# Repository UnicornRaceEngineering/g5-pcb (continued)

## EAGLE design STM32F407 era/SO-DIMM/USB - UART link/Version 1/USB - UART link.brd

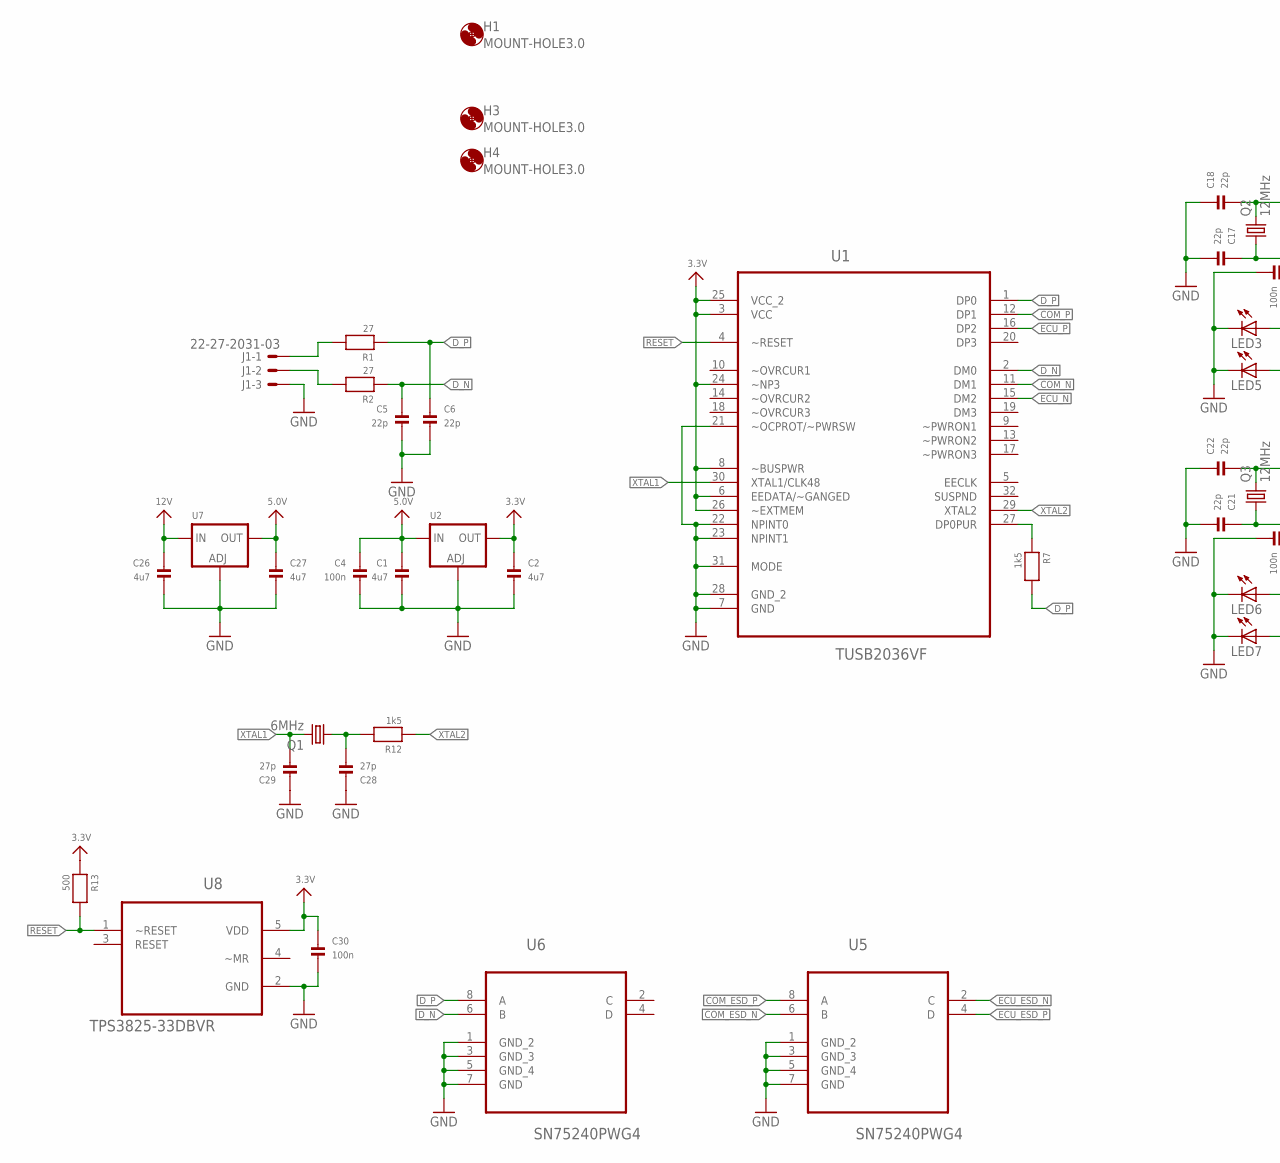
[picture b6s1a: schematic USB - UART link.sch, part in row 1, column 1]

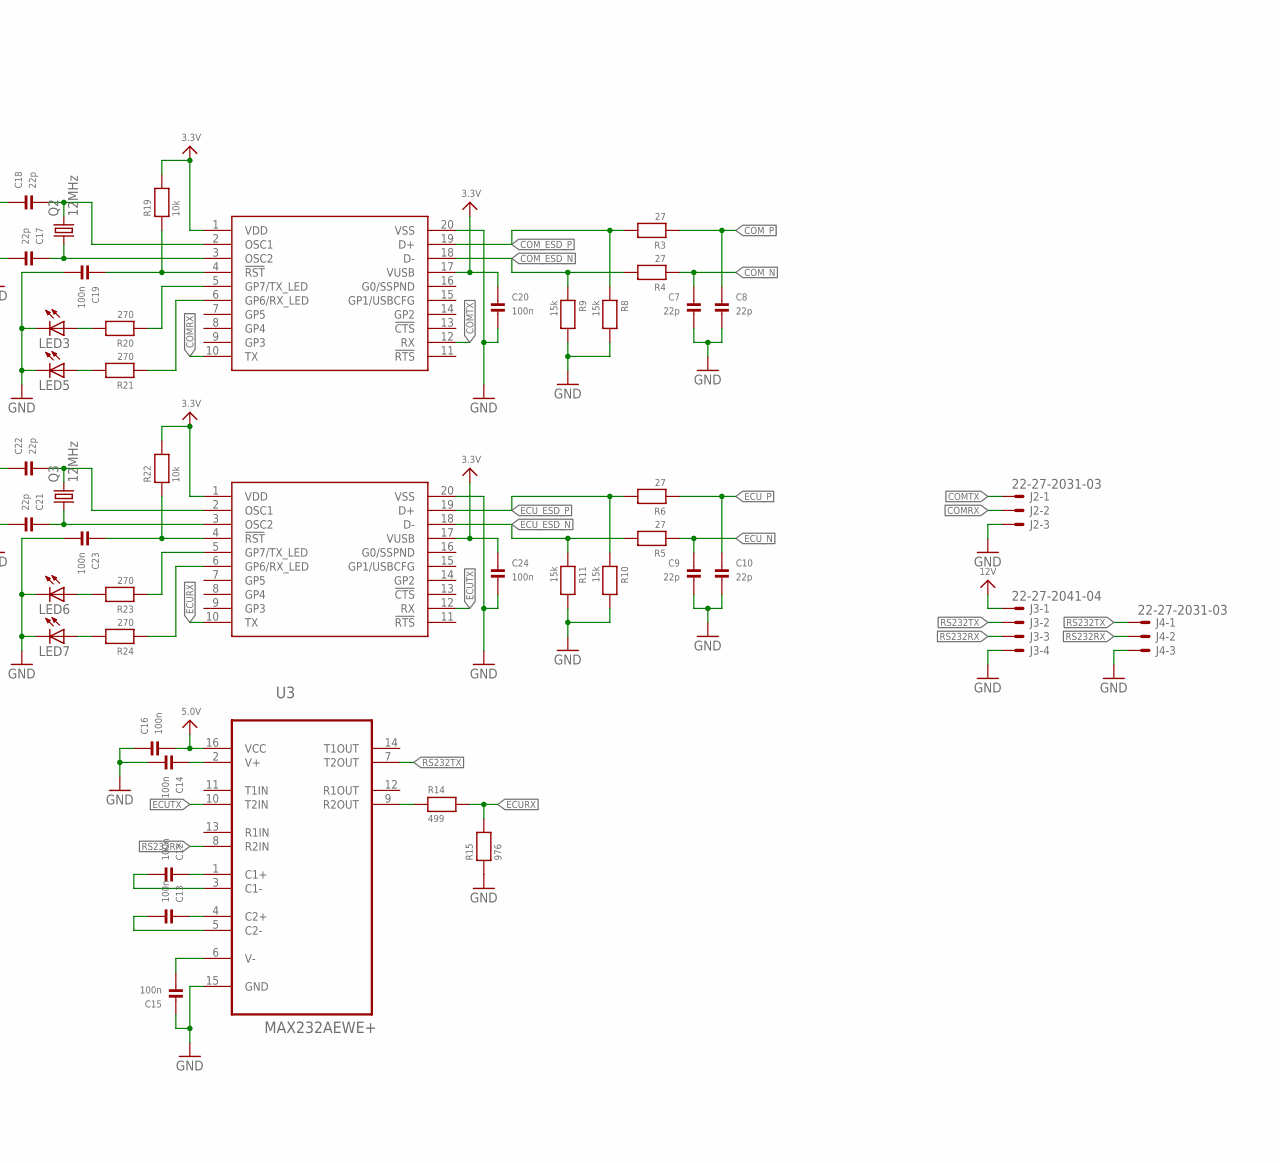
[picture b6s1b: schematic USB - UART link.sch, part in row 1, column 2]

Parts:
C1, C2, C26, C27: 4u7; _0805
C4, C12, C13, C14, C15, C16, C19, C20, C23, C24, C30: 100n; _0603
C5, C6, C7, C8, C9, C10, C17, C18, C21, C22: 22p; _0603
C28, C29: 27p; _0603
H1, H3, H4: MOUNT-HOLE3.0; 3,0
J1, J2, J4: 22-27-2031-03; 6410-03
J3: 22-27-2041-04; 6410-04
LED3, LED5, LED6, LED7: LEDCHIPLED_0805; CHIPLED_0805
Q1: 6MHz; HC49/S
Q2, Q3: 12MHz; HC49/S
R1, R2, R3, R4, R5, R6: 27; _0603
R7, R12: 1k5; _0603
R8, R9, R10, R11: 15k; _0603
R13: 500; _0603
R14: 499; _0603
R15: 976; _0603
R19, R22: 10k; _0603
R20, R21, R23, R24: 270; _0603
U1: TUSB2036VF; QFP80P900X900X145-32N
U2, U7: LM1117SOT223-REFLOW; SOT223-R
U3: MAX232AEWE+; SOIC127P1032X265-16N
U5, U6: SN75240PWG4; SOP65P640X120-8N
U8: TPS3825-33DBVR; SOT95P280X145-5N
U$24, U$29: MCP2200; SO20L

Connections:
3.3V: C2.1, C20.1, C24.1, C30.1, R13.1, R19.2, R22.2, U1.3 (VCC), U1.6 (EEDATA/~GANGED), U1.8 (~BUSPWR), U1.24 (~NP3), U1.25 (VCC_2), U1.26 (~EXTMEM), U2.2 (OUT), U8.5 (VDD), U$24.1 (VDD), U$24.17 (VUSB), U$29.1 (VDD), U$29.17 (VUSB)
5.0V: C1.1, C4.1, C16.2, C27.1, U2.3 (IN), U3.16 (VCC), U7.2 (OUT)
12V: C26.1, J3.1, U7.3 (IN)
COMRX: J2.2, U$24.10 (TX)
COMTX: J2.1, U$24.12 (RX)
COM_ESD_N: R4.2, R9.1, U5.6 (B), U$24.18 (D-)
COM_ESD_P: R3.2, R8.1, U5.8 (A), U$24.19 (D+)
COM_N: C7.1, R4.1, U1.11 (DM1)
COM_P: C8.1, R3.1, U1.12 (DP1)
DO_N: J1.2, R2.2
DO_P: J1.1, R1.2
D_N: C5.1, R2.1, U1.2 (DM0), U6.6 (B)
D_P: C6.1, R1.1, R7.2, U1.1 (DP0), U6.8 (A)
ECURX: R14.2, R15.2, U$29.10 (TX)
ECUTX: U3.10 (T2IN), U$29.12 (RX)
ECU_ESD_N: R5.2, R11.1, U5.2 (C), U$29.18 (D-)
ECU_ESD_P: R6.2, R10.1, U5.4 (D), U$29.19 (D+)
ECU_N: C9.1, R5.1, U1.15 (DM2)
ECU_P: C10.1, R6.1, U1.16 (DP2)
GND: C1.2, C2.2, C4.2, C5.2, C6.2, C7.2, C8.2, C9.2, C10.2, C14.2, C15.1, C16.1, C17.2, C18.1, C19.2, C20.2, C21.2, C22.1, C23.2, C24.2, C26.2, C27.2, C28.1, C29.1, C30.2, J1.3, J2.3, J3.4, J4.3, LED3.C, LED5.C, LED6.C, LED7.C, R8.2, R9.2, R10.2, R11.2, R15.1, U1.7 (GND), U1.21 (~OCPROT/~PWRSW), U1.22 (NPINT0), U1.23 (NPINT1), U1.28 (GND_2), U1.31 (MODE), U2.1 (ADJ), U3.15 (GND), U5.1 (GND_2), U5.3 (GND_3), U5.5 (GND_4), U5.7 (GND), U6.1 (GND_2), U6.3 (GND_3), U6.5 (GND_4), U6.7 (GND), U7.1 (ADJ), U8.2 (GND), U$24.20 (VSS), U$29.20 (VSS)
unnamed: R14.1, U3.9 (R2OUT)
unnamed: R7.1, U1.27 (DP0PUR)
unnamed: C13.1, U3.4 (C2+)
unnamed: C12.2, U3.3 (C1-)
unnamed: C12.1, U3.1 (C1+)
unnamed: C28.2, Q1.1, R12.2
unnamed: C15.2, U3.6 (V-)
unnamed: C14.1, U3.2 (V+)
unnamed: C13.2, U3.5 (C2-)
unnamed: C22.2, Q3.2, U$29.2 (OSC1)
unnamed: C18.2, Q2.2, U$24.2 (OSC1)
unnamed: C17.1, Q2.1, U$24.3 (OSC2)
unnamed: C21.1, Q3.1, U$29.3 (OSC2)
unnamed: R21.1, U$24.6 (GP6/RX_LED)
unnamed: R20.1, U$24.5 (GP7/TX_LED)
unnamed: C19.1, R19.1, U$24.4 (!RST)
unnamed: R24.1, U$29.6 (GP6/RX_LED)
unnamed: R23.1, U$29.5 (GP7/TX_LED)
unnamed: LED3.A, R20.2
unnamed: LED5.A, R21.2
unnamed: C23.1, R22.1, U$29.4 (!RST)
unnamed: LED6.A, R23.2
unnamed: LED7.A, R24.2
RESET: R13.2, U1.4 (~RESET), U8.1 (~RESET)
RS232RX: J3.3, J4.2, U3.8 (R2IN)
RS232TX: J3.2, J4.1, U3.7 (T2OUT)
XTAL1: C29.2, Q1.2, U1.30 (XTAL1/CLK48)
XTAL2: R12.1, U1.29 (XTAL2)

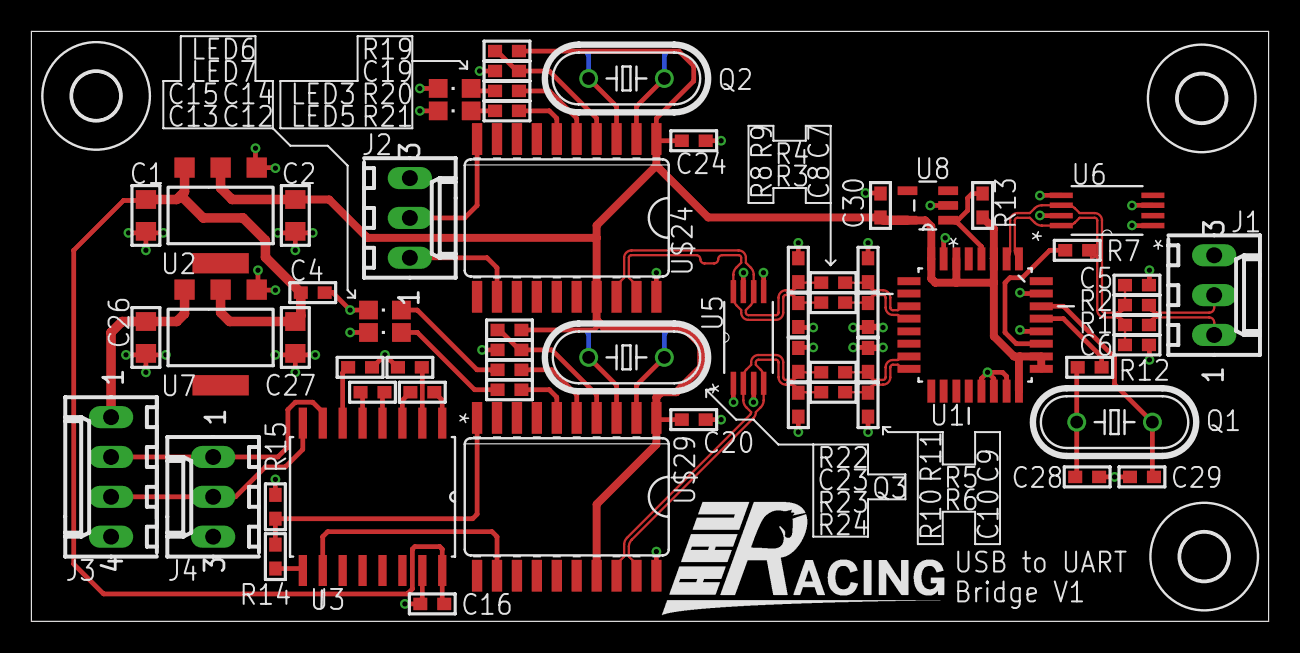
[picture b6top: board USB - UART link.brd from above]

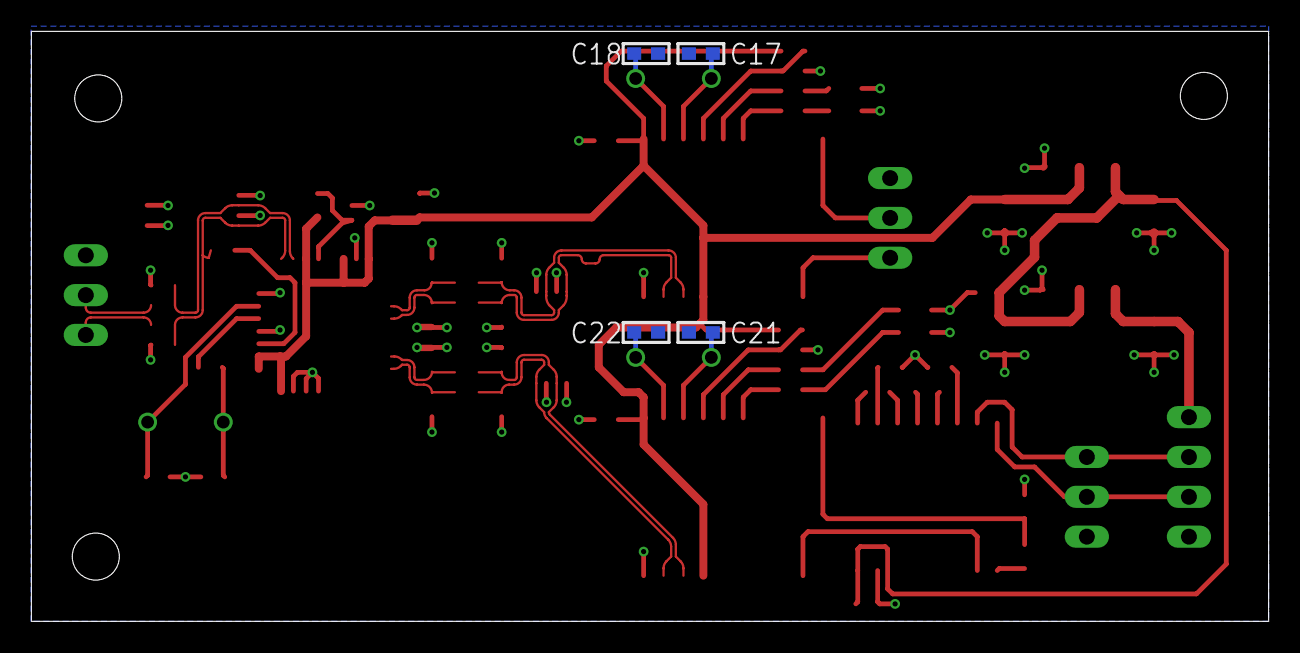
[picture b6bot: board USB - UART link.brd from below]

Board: 2 copper layers, 78.9 x 37.6 mm, 71 parts (4 on the bottom side), 48 nets.

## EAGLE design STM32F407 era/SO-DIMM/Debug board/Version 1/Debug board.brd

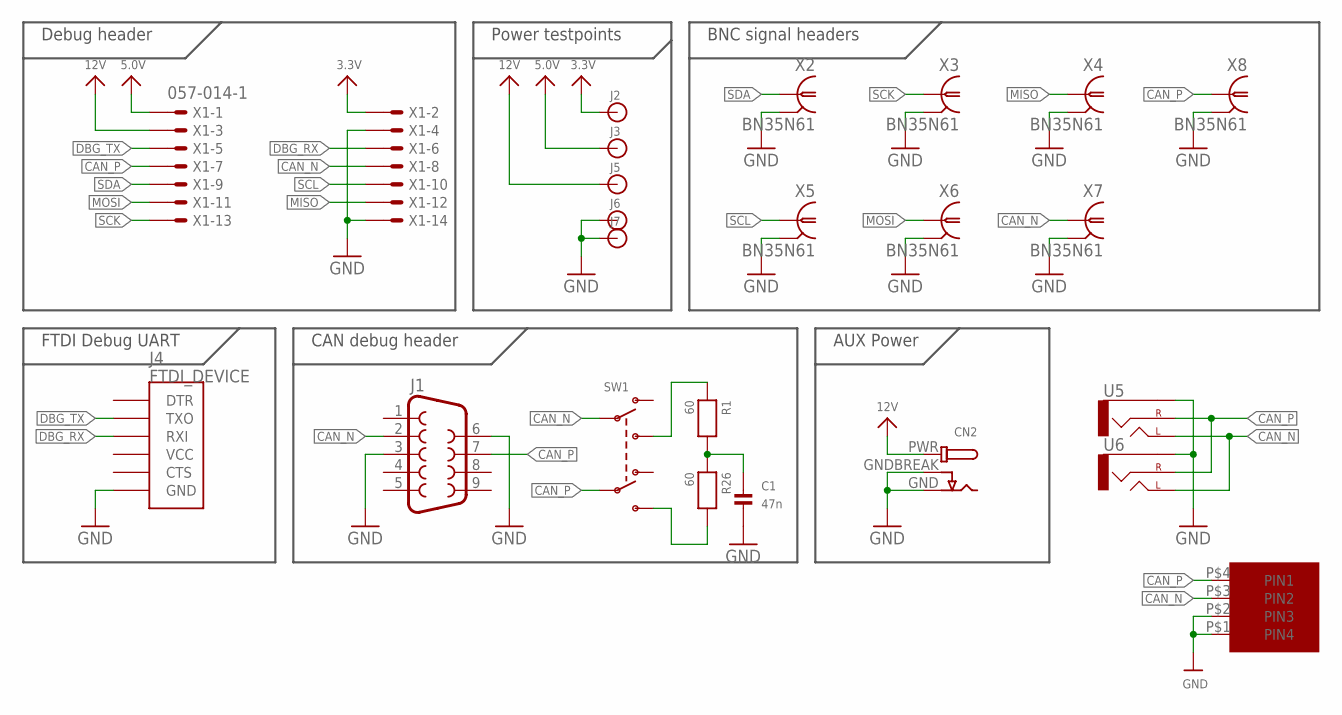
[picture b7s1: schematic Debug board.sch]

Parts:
C1: 47n; _0603
CN2: DCBARRELPTH; DCJACK_2MM_PTH
J1: DB9FEMALE; DB9
J2, J3, J5, J6, J7: BANANA_CONN
J4: FTDI_DEVICE; FTDI_DEVICE_SIDE
R1, R26: 60; _0603
SW1: SWITCH_DPDT; DPDT_SMT_JS202011SCQN
U5, U6: AUDIO-JACKPTH; AUDIO-JACK
U$21: MICROFIT4; 43045-0400
X1: 057-014-1
X2, X3, X4, X5, X6, X7, X8: BN35N61; B35N61

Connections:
3.3V: J2.P$1, X1.2
5.0V: J3.P$1, X1.1
12V: CN2.PWR, J5.P$1, X1.3
CAN_N: J1.2, SW1.P$2 (P1), U5.TIP (LEFT), U6.TIP (LEFT), U$21.P$3 (PIN2), X1.8, X7.1
CAN_P: J1.7, SW1.P$5 (P2), U5.RING (RIGHT), U6.RING (RIGHT), U$21.P$4 (PIN1), X1.7, X8.1
DBG_RX: J4.P$3 (RXI), X1.6
DBG_TX: J4.P$2 (TXO), X1.5
GND: C1.2, CN2.GND, CN2.GNDBREAK, J1.3, J1.6, J4.P$6 (GND), J6.P$1, J7.P$1, U5.SLEEVE, U6.SLEEVE, U$21.P$1 (PIN4), U$21.P$2 (PIN3), X1.4, X1.14, X2.2 (GND), X2.3 (GND), X2.4 (GND), X2.5 (GND), X3.2 (GND), X3.3 (GND), X3.4 (GND), X3.5 (GND), X4.2 (GND), X4.3 (GND), X4.4 (GND), X4.5 (GND), X5.2 (GND), X5.3 (GND), X5.4 (GND), X5.5 (GND), X6.2 (GND), X6.3 (GND), X6.4 (GND), X6.5 (GND), X7.2 (GND), X7.3 (GND), X7.4 (GND), X7.5 (GND), X8.2 (GND), X8.3 (GND), X8.4 (GND), X8.5 (GND)
MISO: X1.12, X4.1
MOSI: X1.11, X6.1
unnamed: C1.1, R1.2, R26.1
unnamed: R1.1, SW1.P$3 (S1)
unnamed: R26.2, SW1.P$4 (S2)
SCK: X1.13, X3.1
SCL: X1.10, X5.1
SDA: X1.9, X2.1

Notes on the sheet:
FTDI Debug UART
Debug header
Power testpoints
CAN debug header
BNC signal headers
AUX Power

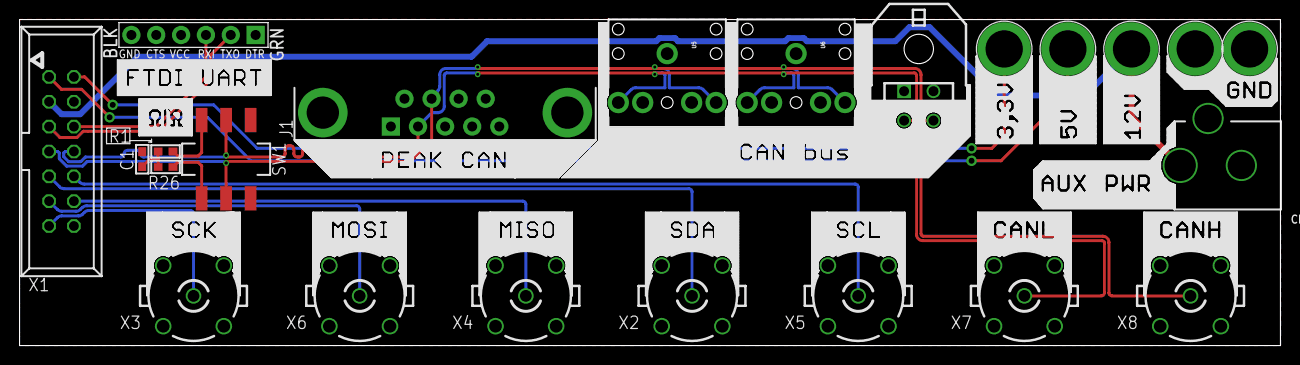
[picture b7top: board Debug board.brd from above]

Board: 2 copper layers, 128.9 x 33.3 mm, 23 parts (0 on the bottom side), 16 nets.

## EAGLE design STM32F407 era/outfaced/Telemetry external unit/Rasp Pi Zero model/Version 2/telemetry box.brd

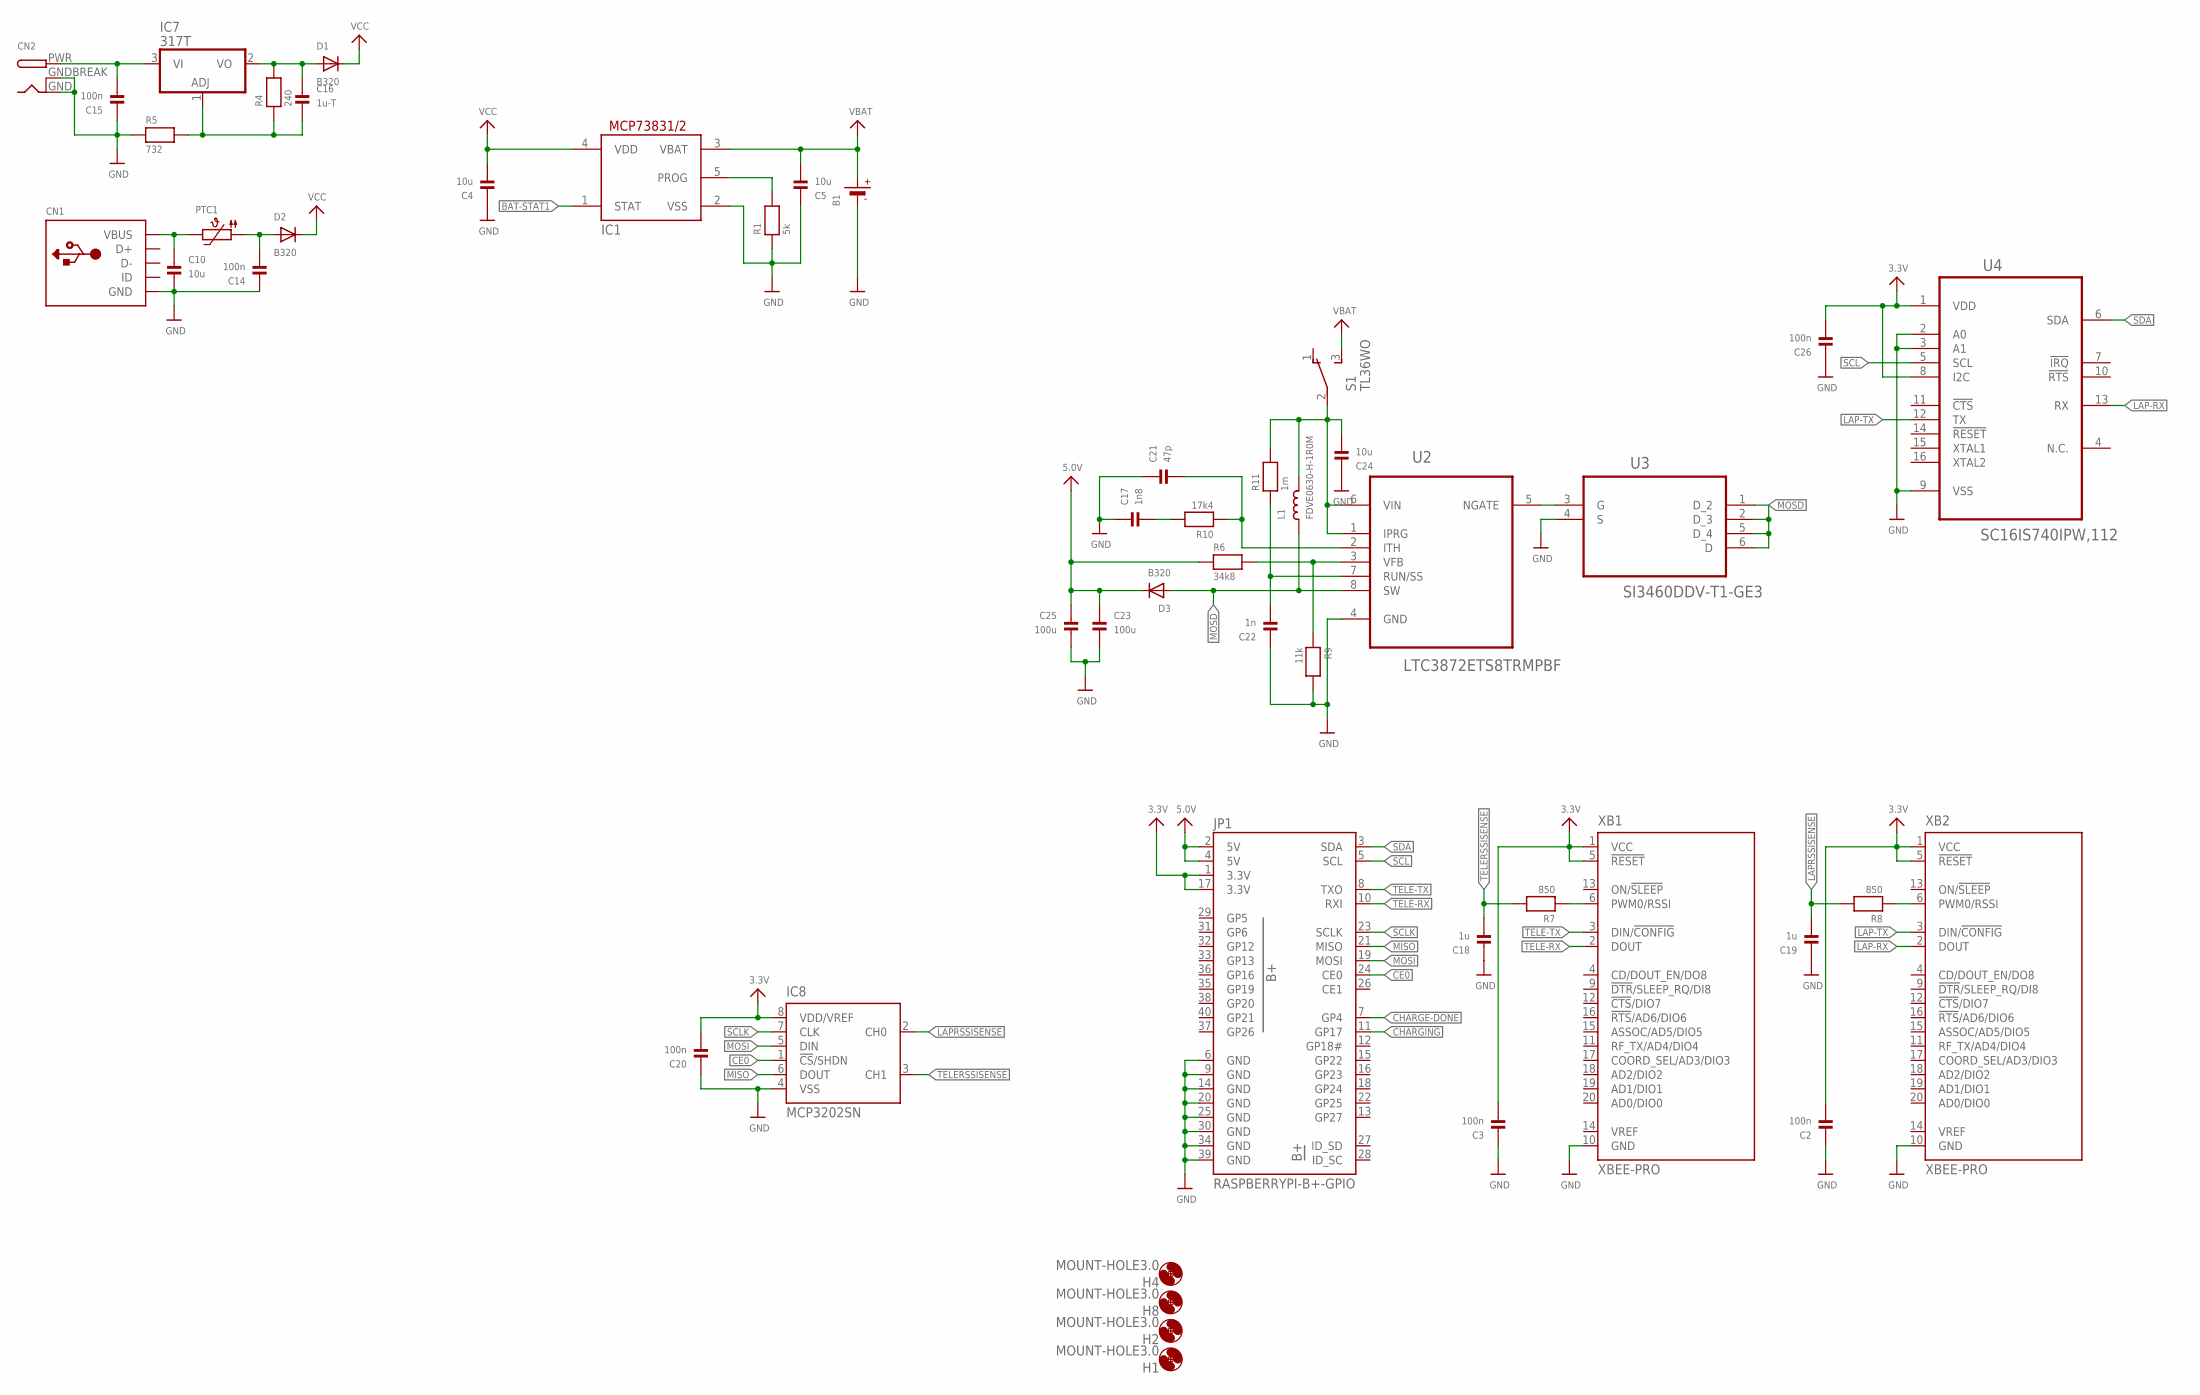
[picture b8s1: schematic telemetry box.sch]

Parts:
B1: BATTERY; JSTPH2
C2, C3, C14, C15, C20, C26: 100n; _0603
C4, C5, C10, C24: 10u; _0805
C16: 1u-T; _0603
C17: 1n8; _0603
C18, C19: 1u; _0603
C21: 47p; _0603
C22: 1n; _0603
C23, C25: 100u; 1206
CN1: USBMINIB; USB-MINIB
CN2: DCBARRELPTH; DCJACK_2MM_PTH
D1, D2, D3: B320; SMADIODE
H1, H2, H4, H8: MOUNT-HOLE3.0; 3,0
IC1: MCP73831/OT; SOT23-5L
IC7: 317T; TO220H
IC8: MCP3202SN; SO-08
JP1: RASPBERRYPI-B+-GPIO; 2X20-SHROUDED
L1: FDVE0630-H-1R0M; INDUCTOR_6X6MM_TDK_SLF6045
PTC1: PTC1206; 1206
R1: 5k; _0603
R4: 240; _0603
R5: 732; _0603
R6: 34k8; _0603
R7, R8: 850; _0603
R9: 11k; _0603
R10: 17k4; _0603
R11: 1m; _0603
S1: TL36WO; TL3XWO
U2: LTC3872ETS8TRMPBF; SOT65P280X100-8N
U3: SI3460DDV-T1-GE3; SOT95P285X110-6N
U4: SC16IS740IPW,112; SOP65P640X110-16N
XB1, XB2: XBEE-PRO

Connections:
3.3V: C2.2, C3.2, C20.2, C26.2, IC8.8 (VDD/VREF), JP1.1 (3.3V), JP1.17 (3.3V), U4.1 (VDD), U4.8 (I2C), XB1.1 (VCC), XB1.5 (!RESET), XB2.1 (VCC), XB2.5 (!RESET)
5.0V: C23.1, C25.1, D3.C, JP1.2 (5V), JP1.4 (5V), R6.1
BAT-STAT1: IC1.1 (STAT)
CE0: IC8.1 (!CS!/SHDN), JP1.24 (CE0)
CHARGE-DONE: JP1.7 (GP4)
CHARGING: JP1.11 (GP17)
GND: B1.1 (-), C2.1, C3.1, C4.1, C5.1, C10.2, C14.1, C15.1, C17.1, C18.1, C19.1, C20.1, C21.1, C22.1, C23.2, C24.1, C25.2, C26.1, CN1.GND, CN2.GND, CN2.GNDBREAK, IC1.2 (VSS), IC8.4 (VSS), JP1.6 (GND), JP1.9 (GND), JP1.14 (GND), JP1.20 (GND), JP1.25 (GND), JP1.30 (GND), JP1.34 (GND), JP1.39 (GND), R1.1, R5.1, R9.2, U2.4 (GND), U3.4 (S), U4.2 (A0), U4.3 (A1), U4.9 (VSS), XB1.10 (GND), XB2.10 (GND)
LAP-RX: U4.13 (RX), XB2.2 (DOUT)
LAP-TX: U4.12 (TX), XB2.3 (DIN/!CONFIG)
LAPRSSISENSE: C19.2, IC8.2 (CH0), R8.2
MISO: IC8.6 (DOUT), JP1.21 (MISO)
MOSD: D3.A, L1.P$1 (1), U2.8 (SW), U3.1 (D_2), U3.2 (D_3), U3.5 (D_4), U3.6 (D)
MOSI: IC8.5 (DIN), JP1.19 (MOSI)
unnamed: C24.2, L1.P$2 (2), R11.2, S1.2, U2.1 (IPRG), U2.6 (VIN)
unnamed: IC1.5 (PROG), R1.2
unnamed: C10.1, CN1.VBUS, PTC1.2
unnamed: C16.2, IC7.1 (ADJ), R4.1, R5.2
unnamed: R6.2, R9.1, U2.3 (VFB)
unnamed: C16.1, D1.A, IC7.2 (VO), R4.2
unnamed: C14.2, D2.A, PTC1.1
unnamed: C15.2, CN2.PWR, IC7.3 (VI)
unnamed: R7.1, XB1.6 (PWM0/RSSI)
unnamed: R8.1, XB2.6 (PWM0/RSSI)
unnamed: U2.5 (NGATE), U3.3 (G)
unnamed: C17.2, R10.2
unnamed: C21.2, R10.1, U2.2 (ITH)
unnamed: C22.2, R11.1, U2.7 (RUN/SS)
SCL: JP1.5 (SCL), U4.5 (SCL)
SCLK: IC8.7 (CLK), JP1.23 (SCLK)
SDA: JP1.3 (SDA), U4.6 (SDA)
TELE-RX: JP1.10 (RXI), XB1.2 (DOUT)
TELE-TX: JP1.8 (TXO), XB1.3 (DIN/!CONFIG)
TELERSSISENSE: C18.2, IC8.3 (CH1), R7.2
VBAT: B1.2 (+), C5.2, IC1.3 (VBAT), S1.3 (S)
VCC: C4.2, D1.C, D2.C, IC1.4 (VDD)

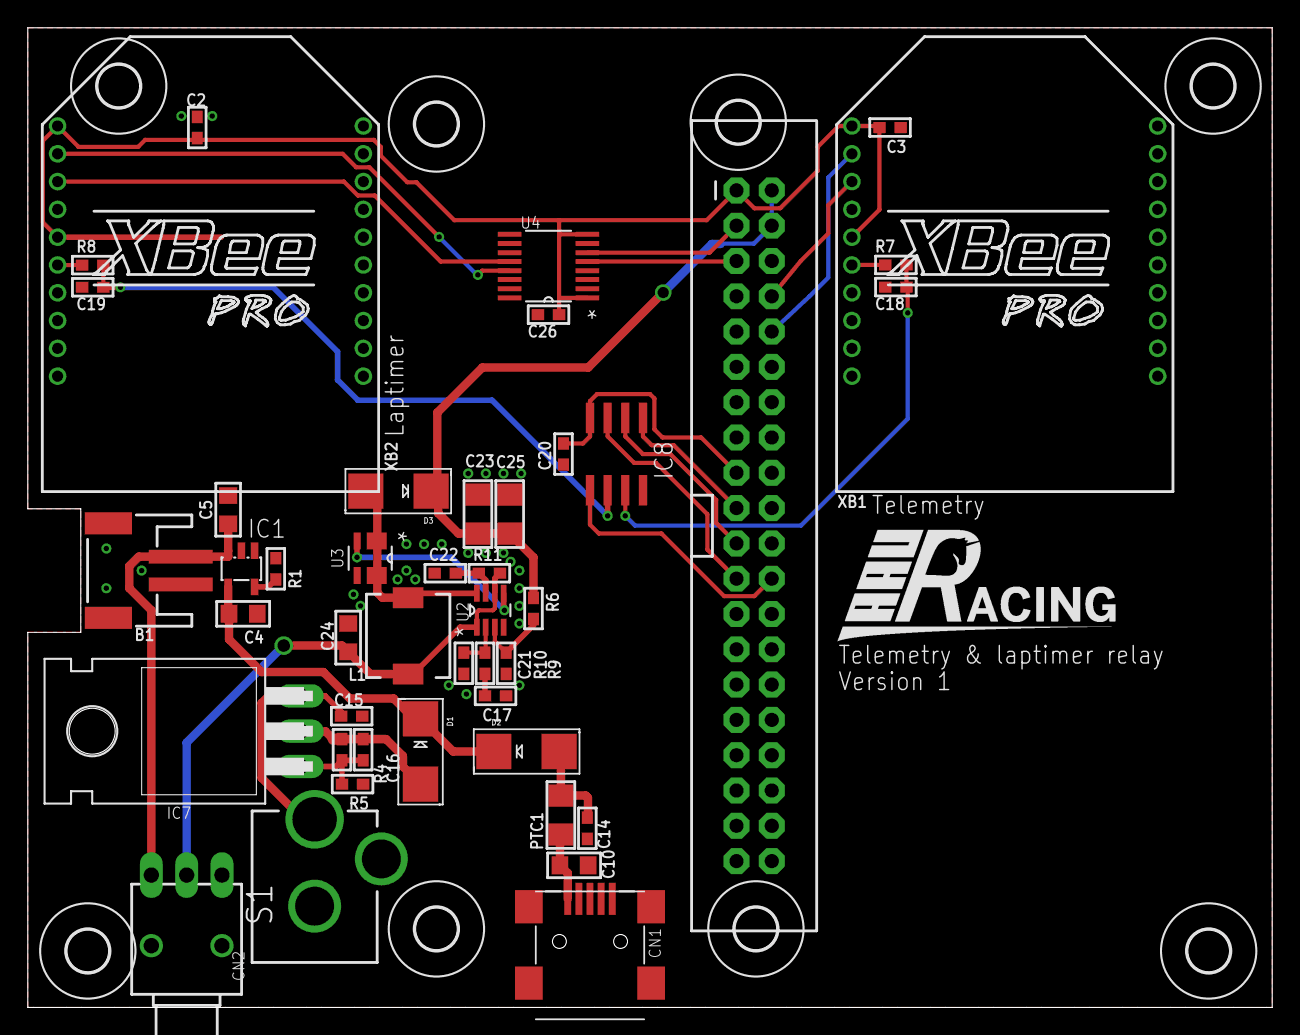
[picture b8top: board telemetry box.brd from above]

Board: 2 copper layers, 89.5 x 70.5 mm, 53 parts (0 on the bottom side), 32 nets.

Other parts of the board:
H3, H5, H6, H7: MOUNT-HOLE3.0; 3,0

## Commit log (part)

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2014-02-27 Added Creative Commons license
2014-02-27 Eagle folder from old repository
2014-03-13 Starting the eagle drawings for the steering wheel display
2014-03-17 changes to the schematic and board layout
2014-03-17 more changes to steering wheel display
2014-03-26 more changes
2014-03-30 changes to display layout
    - Added shift light
    - adjusted position of drillholes to take into account the size of the
    buttons and the fotary switch
    - added the connectors for the buttons (might have to be redonee)
2014-03-31 changes
    changes
2014-03-31 changes to the board
    added the side mounted burn port
2014-04-09 added pull down resistors to buttons
2014-04-10 added new led driver
2014-04-10 uerrt
2014-04-15 her peter
    her peter
2014-04-15 til peter
    padsfokadfoojdsf
2014-04-15 edited small parts
2014-04-15 test
2014-04-15 final changes
2014-04-24 materials liste
2014-05-27 random update
2014-05-27 random update nummer 2
2014-05-27 number 3
2014-05-27 name update
    added desciptive names to signal lanes for better clarification
2014-06-29 minor preperations for wiring G5
2014-06-29 minor change again in layout of dev board
2014-06-29 and again
2014-06-29 is this broken
2014-07-22 minor fix
2014-08-22 added lib file for IR2106
2014-08-22 Simple schematic for H-brigde Allmost done.
2014-08-23 Shield updates
    Added another I2C port on the shield
2014-08-23 finalized v1 of board
2014-08-25 minor update to DUE shield
2014-09-09 overview update
2015-02-12 Major Cleanup and folder structure change
    Rearranged the old boards and layouts to new folder called 'AT90CAN128
    era and older', created a new folder for 'STM32F407 era', Datasheets and
    a folder with a good bunch of eagle libraries including one which have
    the correct STM32 chip (horay!) and finally the Steering wheel V2 has
    finally come out of hiding, though it still ned to be redrawn to STM32
    instead of AT90.
2015-02-14 Redrawn the V2 of steering wheel to use ARM
    Steering wheel V2 has been redrawn to use STM32F407 instead of the old
    AT90CAN128.
    Needs to be proberly looked through for any errors and oversights
2015-02-14 added cutout for jtag header.
2015-02-17 started working on the raspberry pi hat for tele
2015-02-18 Initial Rasp Pi UPS design done
2015-02-19 minor changes
2015-02-24 changes to the charging circuit
2015-03-01 changes to battery board
2015-03-01 Minor changes to utility hat
2015-03-01 added Switching power supply to telemtry battery board
2015-03-19 added bracing PCB for rotational switch
2015-03-19 Now treat generated files as binary.
    This should make diffs more clear
2015-03-19 added processor board
    started development of the STM32F4 processor board
2015-03-19 Added peripfial ports to processor port
    added connections for CAN. USB. JTAG; I2C, SPI.
    Added crystal, and decoupling circuitry
2015-03-20 continued work on processor board
    started doing the layout for the board and startet to add the
    interfacing pin rows.
2015-03-21 finished v 0.1 of processor board layout
    TA DAAAAAA!
2015-03-22 finished v 0.5 of processsor board
    Did some cleaning of the pin busses, and some small components
    placements cleanup.
    Added Unicorn Logo and board name to silkscreen
2015-03-23 Silkscreen cleanup
    tried to make the silkscreen look a little more usefull, especially
    after the old steeringwheel fuckup, (shits was confusing yo)
2015-03-23 created an JTAG adapter
    Created and JTAG adapter to fit the 20-pin JTAG used by the programmer
    to the 10-pin JTAG connection used by the CPU board
2015-03-23 minor change to JTAG apdapter layout (because OCD)
2015-03-24 updates to silkscreen
2015-03-25 created library file of CPU board for ease of use
    created an library file for the CPU board for ease of use with
    development of extension boards
2015-03-26 added laptiming circuit
2015-03-26 started redoing the layout for the new alu housing
2015-03-28 continued work on the layout
2015-03-29 silkscreen and layout cleanu
2015-04-07 layout updates to fit 2 xbees
2015-04-11 last layout update for V1
2015-04-12 started development on the development board
2015-04-14 Continued work on dev board layout
2015-04-21 updates to the layout and done routing (maybe)
2015-04-23 removed second xbee
2015-04-28 updates to layout
2015-05-05 fixed typo
2015-05-07 small updates for etching
2015-05-10 library updates and layout updates
2015-05-10 layout updates
2015-05-12 preperations for etching
2015-05-12 layout update, and added power switch
2015-06-02 updates for pcb production
2015-06-12 minor updates to board layout
    Added USB power fuse, and added toggle switch for boot switch
2015-06-24 redid power circuitry to accomondate oversight
    forget the laser needed 5V DOH!
2015-08-20 updated LED drivers
    Updated the LED drivers to Constant Current drivers
2015-08-20 Schematic for communication board
2015-08-20 Schematic
    Påbegyndt af Jesper
2015-08-26 added Wired version
    Started working on a Wired version of the laptiming system
2015-08-27 started work on LCD dashboard
2015-09-03 startet working on seven segment version
2015-09-03 Added RPM leds and constant current IC's
2015-10-06 minor updates
2015-10-07 started work on traction control node
2015-10-08 added dashboard control buttons
    added buttons to add functionality to the LCD panel
2015-10-08 more work on TC, startet work on Aux sensor board
2015-10-11 more work done on routing
2015-10-13 fixed errors on dev board
2015-10-15 merged TC board with AUX board
2015-10-29 The new exports should fit in size!
2015-11-03 First schematic revision for com-node done
2015-11-03 fixed CPU board header in library and dev board
2015-11-09 Exports which fits in size
2015-11-09 Exported without keep-out
2015-11-09 Export without keep-out
2015-11-25 change impendance layout for CAN transciever
2015-11-30 started development on new telemetry unit
    started working in rasp pi zero design
2015-12-01 added hardware debounce circuit to buttons
2015-12-01 started reworking the board for better charging
    started reworking the battery solution to incorporate parallel cell
    charging.
2015-12-01 Update on board
    Still some ERC warnings to solve
2015-12-02 small cosmic changes
2015-12-19 minor changes to layout
2015-12-21 succeded in removing one of 2 connectors
2015-12-21 moved outfaced boards to new folder
2015-12-21 Can't get the last error removed...
2015-12-21 started working on the power circuitry
    started work on 5V boost circuit for the battery powered operation
2015-12-21 fexed last CRC errors
2015-12-21 added 5V boost circuit for tele unit
    also should be done now
2015-12-22 Schematic finished + placement of components on board
2015-12-24 added CAN bus connections to TC board
2015-12-24 small change to board routing
2016-01-02 Com node finished
    Finished and routed for final check
2016-01-02 fixed small layout errors
2016-01-14 finished adding gear feedback circuit
2016-02-22 prepping boards for production
2016-02-23 more final board prepping for production
2016-02-23 change in power circuit
2016-02-24 last board done with silkscreen prep for production
2016-02-28 added hardware debounce and added room for SD card on rasp pi
2016-03-01 added the CAM file for GERBER file creation
2016-03-01 created the last sets of GERBER files for production
2016-03-22 gerber files for production
2016-03-31 BOM for components purchase
2016-03-31 added version history folders
2016-03-31 fixed compenent D1 and D2 as noted on Wiki
    http://wiki.aauracing.dk/doku.php?id=biler:g7:elektronik:pcb_version_1
2016-04-03 Folder cleanup and more V1 error fixin
2016-04-03 more fixes for V2 as noted on wiki
2016-04-12 added brakeligt
2016-05-03 csv files for easier soldering
2016-06-23 opdatering af BOM lister
2016-06-23 started work on V3
2016-06-28 continued work onTC V2
2016-06-28 Revert "started work on TC V2"
    This reverts commit da86986705d51cbc4691d6d7bad1c5aae1ca4806.
2016-06-29 started work on alternative LCD module
2016-07-03 more work on better layout for V3
2016-07-05 started work on alternativ LCD solution
2016-08-02 more work on TC, first layout of 3G test board
2016-08-02 board layout changes to H-Bridge power
2016-08-17 more work on V2 and folder cleanup
    Folder clenup for boards with coming V2's (most likely)
    V2 work:
    - Dev board:
    - added version folders for further expansion
    - MCU board:
    - added version 3 folder
2016-08-23 more layout work done with added verison for seperate PCB box housing
2016-08-23 added pinout sheet for PCB box
2016-09-01 tiny layout changes to power
2016-09-04 further layout work done
2016-09-09 better layout for analog buffers
2016-09-11 changed H-Bridge design for modular mount, more layout on TC
2016-09-19 more layout done to PCB
2016-09-22 starting to finish the layout
2016-09-26 finished RC
2016-10-05 creating images for Wiki dokumentation
2016-10-07 fixed silkscreen and added extra button for interface
2016-10-10 started work on V2
2016-10-10 added physical board shape to v2
2016-10-12 added mPCIe header for 3G module
2016-10-16 continued work
    started work on wireless lap timer with LoRa
    added RS232 and USB-UART to com node
2016-10-18 com node board size to small, working on bigger
2016-10-20 continued layout work for com node
    added usb conversion chip for ECU for easier connectivity from external
    source
2016-10-22 laptimer RC done, com node (done) need checkup
2016-10-25 silkscreen changes
2016-10-27 All boards RC done!
2016-10-28 added improved methods for soldering
2016-10-30 worlds be blazing
2016-11-01 added critcal missing ground connection
2016-11-01 added correct wheel speed sensor ic's and buffer
2016-11-01 more work on wheel speed sensor IC
2016-11-03 continued work with last additions
2016-11-06 work work
2016-11-07 added switch to select int or ADC for oilp
2016-11-08 adding last changes to accomendate changes in H-Bridge
2016-11-08 more changes to new additions
2016-11-09 more work on extra ADC's
2016-11-10 TC RC done, needs recheck
2016-11-13 just needs finishig touches now
2016-11-13 fixed silkscreen
2016-11-20 added 4 16MBit SPI flash for SD card backup
2016-11-22 fixed minor mistakes, added GPS header
2016-12-07 continued work on H-bridge
2016-12-07 H-bridge done
2016-12-11 fixed 12V error with PTC fuse. Started work on new Dev Board
2016-12-13 more work on DEV V2 and added gerber tut on wiki
2017-02-08 replaced DAC for better
2017-03-07 I dont remember
2017-03-12 created Gerbers
2017-03-12 yada
2017-03-12 minor updates to power circuitry
2017-03-14 added testpoints to power rails and coms, and created new Gerbers for PCB order
2017-03-28 DIGITAL POTENTIOMETER
2017-03-28 initial BOM made
2017-04-10 added board count factor to BOM
2017-04-10 added more updates to board count factor
2017-04-11 last update to instock
2017-04-11 Numbers
2017-04-17 BOM update
2017-04-18 Final order for RS + missing things from farnell
2017-05-10 csv for soldering
2017-05-10 started V4 of laptimer
2017-06-18 added LCD datasheet
2017-07-17 i dont know
2017-07-18 Cleaned up folder structure
2017-07-21 More cleanup and getting ready for SODIMM systems
2017-07-26 First draft for SODIMM CPU V1 done
2017-08-03 Started work on new COM-TC module
2017-08-07 more work on COM-TC
2017-08-11 More work on SO-DIMM systems
2017-08-27 update to dash, CPU. more work on COM-TC
    - Dashboard
    Fixed pinout error with overlapping interrupt pins.
    Added missing silkscreen marking
    - CPU
    Added holes for mechanical fastening
2017-09-05 Continued work on dev board and COM-TC
2017-09-08 more work on debug board silkscreen
2017-09-10 added 12V aux power to debug board
2017-09-19 USB to UART done, mork work on COM/TC
2017-09-20 LoPy / Xbee telemtry receiver hybrid done
2017-10-12 All board V1-RC1 done
    all boards ready for inspection
2017-10-12 extra ERC check done
2017-10-16 last end changes on boards
    Dev board
    - Added 8 LED for ekstra debugging feature
    - fixed Tvalue silkscreen
    -
    COM/TC
    - fixed connections om P-channel RPP
2017-10-20 small error fixes
2017-10-23 error corrections
2017-10-26 added accelerometer
2017-12-19 changed schematic for better organized view
2018-01-31 added gerbers for production
2018-02-01 fixed a few error and remade gerbers
2018-02-18 Updated URLs and amounts
